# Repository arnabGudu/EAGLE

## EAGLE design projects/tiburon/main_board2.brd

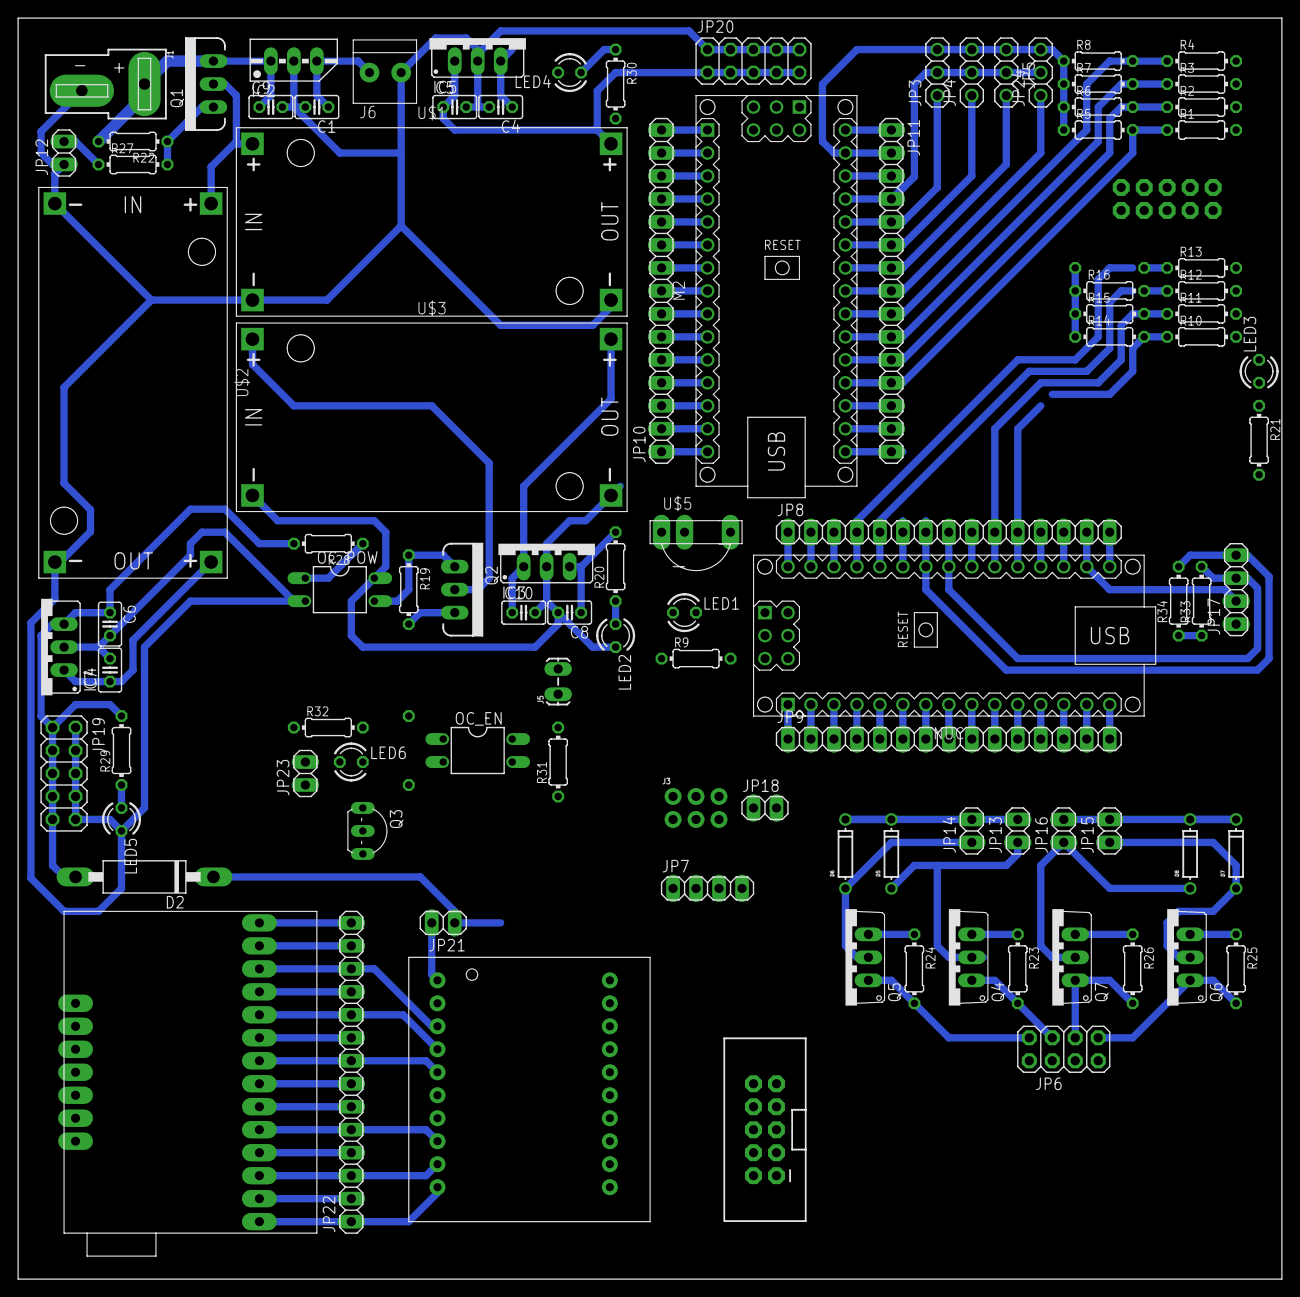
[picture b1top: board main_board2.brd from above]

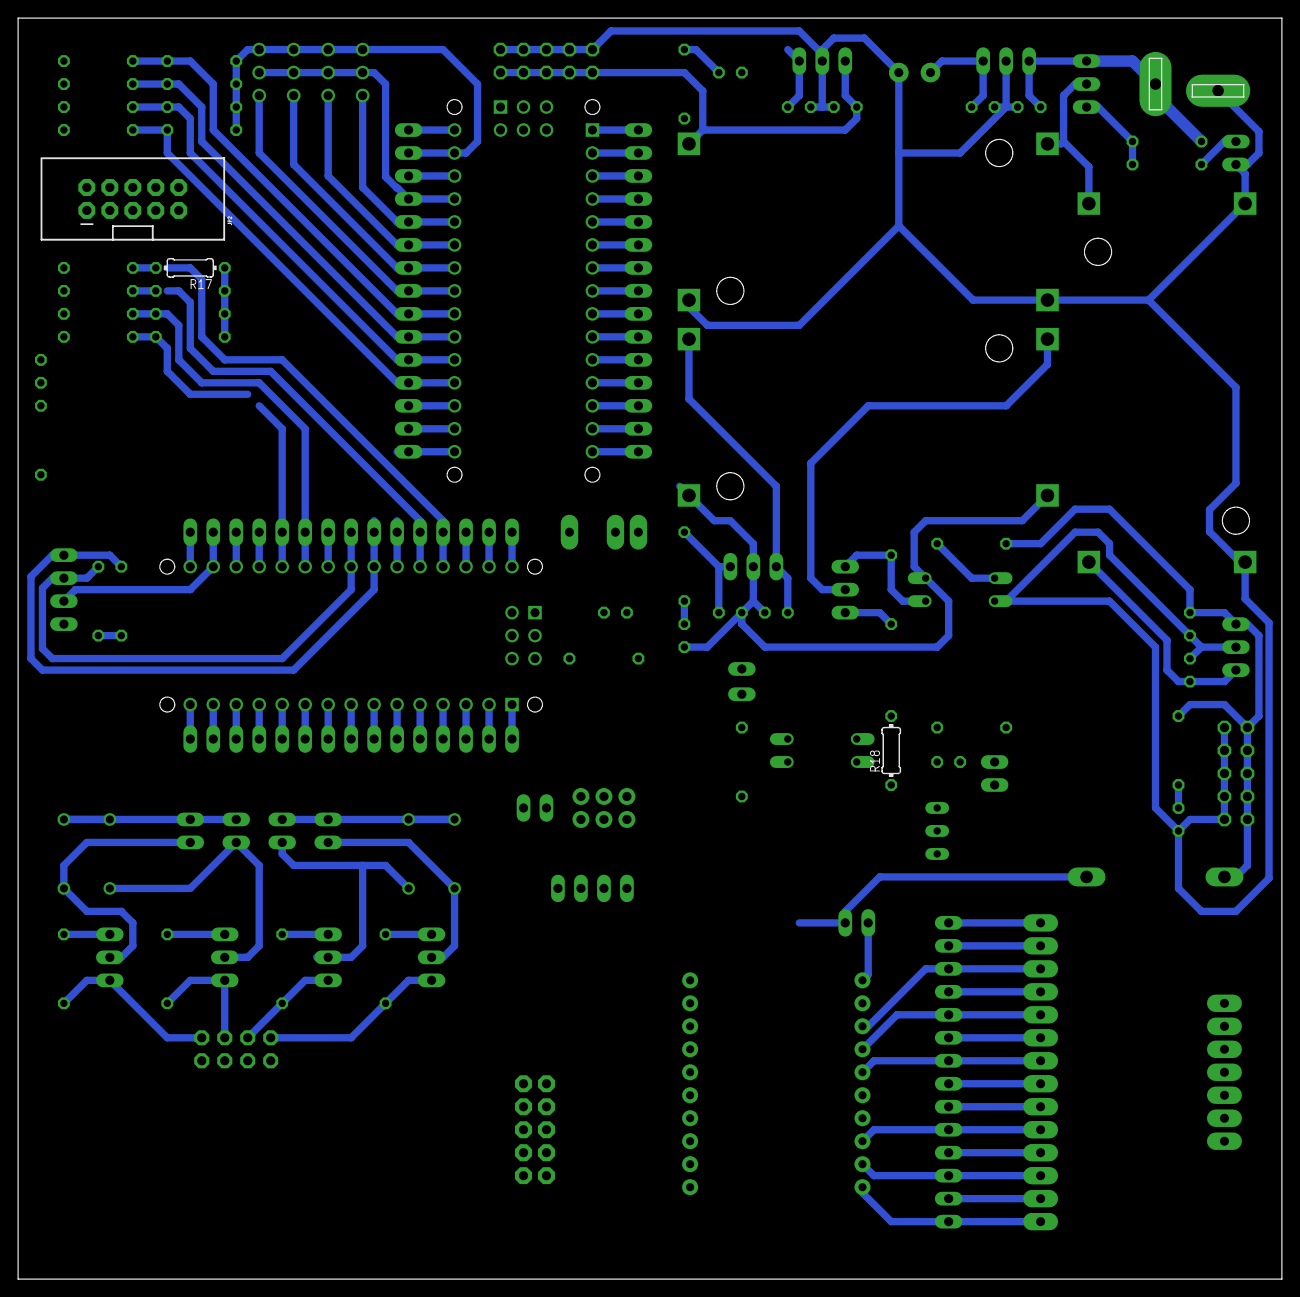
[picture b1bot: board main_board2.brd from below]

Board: 2 copper layers, 139.7 x 139.4 mm, 102 parts (3 on the bottom side), 119 nets.

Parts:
C1, C4, C5, C6, C7, C8, C9, C10: C025-025X050
D2: SCOTTKY; CB417-15
D5, D6, D7, D8: DO-1N4148
IC2: 7812; 78MXXS
IC3, IC4, IC5: 78XXS
J1: DEANS
J3: 2X3-NS
J5: 1X02_LOCK_LONGPADS
J6: 1X2-3.5MM
JP1, JP2: M05X2SHD; 2X5-SHROUDED
JP3, JP4, JP24: 1X03
JP5: Temp Sensor; 1X03
JP6: 2X04
JP7, JP17: 1X04
JP8, JP9, JP10, JP11: 1X15
JP12, JP13, JP14, JP15, JP16, JP21, JP23: 1X02
JP18: Extra Reed; 1X02
JP19, JP20: 2X05
JP22: 1X14
LED1, LED2, LED3, LED4, LED5, LED6: LED3MM
M2: ARDUINO-NANO-3.0#ISP
NUC: ARDUINO-NANO-3.0#ISP
OC_EN: SFH610; DIL04
OC_POW: SFH610; DIL04
Q1, Q2: MOSFET-PCHANNELFQP27P06; TO220V
Q3: BC548; TO92-EBC
Q4, Q5, Q6, Q7: TO220V
R1, R2, R3, R4, R5, R6, R7, R8, R9, R10, R11, R12, R13, R14, R15, R16, R17, R18, R19, R20, R21, R22, R23, R24, R25, R26, R27, R28, R29, R30, R31, R32, R33, R34: 0204/7
U$1, U$2, U$3: DC-DC-STEP-DOWN-LM2596
U$5: TSOP34X; TSOP3XXX
U$6: SERVO_CONTROLLER
U$7: DIGITAL_ISOLATOR; DIGITAL_ISOLATOR_MODULE

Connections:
DR1: JP6.1, Q6.1, R25.2
DR2: JP6.3, Q7.1, R26.2
E16.8V: Q2.3, R19.2
EA0: JP11.12, M2.J2.12, R1.1, R5.2
EA1: JP11.11, M2.J2.11, R2.1, R6.2
EA2: JP11.10, M2.J2.10, R3.1, R7.2
EA3: JP11.9, M2.J2.9, R4.1, R8.2
ED3: JP10.10, M2.J1.6, R9.2
EN: J5.2, OC_EN.4, R31.2
GNDE: C8.2, C10.2, IC3.GND, JP2.2, JP3.3, JP4.3, JP5.3, JP11.2, JP24.3, LED1.K, LED2.K, LED4.K, M2.J2.2, OC_POW.4, Q3.E, R5.1, R6.1, R7.1, R8.1, U$3.IN-, U$3.OUT-, U$7.19
GNDN: C1.2, C4.2, C5.2, C6.2, C7.2, C9.2, IC2.GND, IC4.GND, IC5.GND, J1.-, J6.2, JP2.1, JP8.2, JP12.1, JP17.1, JP18.1, JP19.2, JP19.4, JP19.6, JP19.8, JP19.10, JP20.2, JP20.4, JP20.6, JP20.8, JP20.10, LED3.K, LED5.K, NUC.J2.2, OC_EN.2, OC_POW.2, Q4.3, Q5.3, Q6.3, Q7.3, R14.1, R15.1, R16.1, R17.1, R23.1, R24.1, R25.1, R26.1, U$1.IN-, U$1.OUT-, U$2.IN-, U$2.OUT-, U$5.1, U$6.GND, U$7.2
N6V: C4.1, D7.C, D8.C, IC5.OUT, JP15.2, JP16.2
N12V: C5.1, D5.C, D6.C, IC5.IN, JP13.2, JP14.2, JP20.1, JP20.3, JP20.5, JP20.7, JP20.9, U$1.OUT+
unnamed: JP10.11, M2.J1.5
unnamed: OC_EN.1, R18.1
unnamed: JP9.1, NUC.J1.1
unnamed: JP9.2, NUC.J1.2
unnamed: JP9.3, NUC.J1.3
unnamed: LED1.A, R9.1
unnamed: JP2.10, R1.2
unnamed: JP2.8, R2.2
unnamed: JP2.6, R3.2
unnamed: JP2.4, R4.2
unnamed: JP8.7, JP17.4, NUC.J2.7, R34.2
unnamed: JP8.8, JP17.3, NUC.J2.8, R33.2
unnamed: JP9.4, NUC.J1.4
unnamed: JP9.5, NUC.J1.5
unnamed: JP2.9, R10.2
unnamed: JP2.7, R11.2
unnamed: JP2.5, R12.2
unnamed: JP2.3, R13.2
unnamed: JP9.6, NUC.J1.6
unnamed: OC_POW.3, Q2.1, R19.1
unnamed: JP9.7, NUC.J1.7
unnamed: C10.1, IC3.IN, U$3.OUT+
unnamed: JP22.10, U$6.8, U$7.4
unnamed: Q2.2, U$3.IN+
unnamed: LED2.A, R20.1
unnamed: D2.C, JP8.4, JP21.1, NUC.J2.4
unnamed: Q3.B, R31.1
unnamed: JP9.8, NUC.J1.8
unnamed: JP22.1, U$6.0, U$7.10
unnamed: C9.1, IC2.IN, J1.+, Q1.3, R22.2
unnamed: C1.1, IC2.OUT, J6.1
unnamed: JP22.2, U$6.1
unnamed: JP9.9, NUC.J1.9
unnamed: JP9.10, NUC.J1.10
unnamed: LED4.A, R30.1
unnamed: JP11.1, M2.J2.1
unnamed: JP9.11, NUC.J1.11
unnamed: JP9.12, NUC.J1.12
unnamed: JP9.13, NUC.J1.13
unnamed: JP9.14, NUC.J1.14
unnamed: JP9.15, NUC.J1.15
unnamed: JP22.3, U$6.2, U$7.9
unnamed: J3.6, JP7.3
unnamed: J3.2, JP7.1
unnamed: J3.1, JP7.2
unnamed: J3.5, JP7.4
unnamed: JP8.1, NUC.J2.1
unnamed: JP8.3, NUC.J2.3
unnamed: JP21.2, U$7.1
unnamed: JP8.5, NUC.J2.5
unnamed: JP8.6, NUC.J2.6
unnamed: JP22.4, U$6.3
unnamed: JP22.5, U$6.4, U$7.8
unnamed: JP8.13, NUC.J2.13
unnamed: JP8.14, JP17.2, NUC.J2.14
unnamed: JP8.15, NUC.J2.15, R21.2
unnamed: LED3.A, R21.1
unnamed: JP22.6, U$6.5
unnamed: JP22.7, U$6.+5V(OUT)
unnamed: JP22.8, U$6.6, U$7.5
unnamed: JP22.9, U$6.7
unnamed: Q1.1, R22.1, R27.2
unnamed: JP22.11, U$6.9
unnamed: JP22.12, U$6.10, U$7.3
unnamed: JP22.13, U$6.11
unnamed: JP10.1, M2.J1.15
unnamed: JP10.2, M2.J1.14
unnamed: JP10.3, M2.J1.13
unnamed: JP10.4, M2.J1.12
unnamed: JP10.5, M2.J1.11
unnamed: JP10.6, M2.J1.10
unnamed: JP10.7, M2.J1.9
unnamed: JP10.8, M2.J1.8
unnamed: JP10.9, M2.J1.7
unnamed: JP22.14, U$6.VSRV
unnamed: JP10.12, M2.J1.4
unnamed: JP10.13, M2.J1.3
unnamed: JP10.14, M2.J1.2
unnamed: JP10.15, M2.J1.1
unnamed: JP11.15, M2.J2.15, R30.2
unnamed: JP11.14, M2.J2.14
unnamed: JP11.13, M2.J2.13
unnamed: JP11.3, M2.J2.3
unnamed: D5.A, JP13.1, Q4.2
unnamed: D6.A, JP14.1, Q5.2
unnamed: JP12.2, R27.1
unnamed: D7.A, JP15.1, Q6.2
unnamed: D8.A, JP16.1, Q7.2
unnamed: C7.1, IC4.IN, U$2.OUT+
unnamed: OC_POW.1, R28.1
unnamed: Q1.2, U$1.IN+, U$2.IN+
unnamed: LED5.A, R29.1
unnamed: LED6.K, Q3.C
unnamed: LED6.A, R32.2
NA0: JP8.12, NUC.J2.12, R13.1, R17.2
NA1: JP8.11, NUC.J2.11, R12.1, R16.2
NA2: JP8.10, NUC.J2.10, R11.1, R15.2
NA3: JP8.9, NUC.J2.9, R10.1, R14.2
TMP1: JP11.8, JP24.1, M2.J2.8
TMP2: JP5.1, JP11.7, M2.J2.7
TMP3: JP4.1, JP11.6, M2.J2.6
TMP4: JP3.1, JP11.5, M2.J2.5
TP1: JP6.5, Q4.1, R23.2
TP2: JP6.7, Q5.1, R24.2
VCCE: C8.1, IC3.OUT, J5.1, JP3.2, JP4.2, JP5.2, JP11.4, JP23.1, JP23.2, JP24.2, M2.J2.4, OC_EN.3, R20.2, R32.1, U$7.20
VCCN: C6.1, D2.A, IC4.OUT, JP19.1, JP19.3, JP19.5, JP19.7, JP19.9, R28.2, R29.2, R33.1, R34.1, U$5.2

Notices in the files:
parts and their libraries:
SparkFun-Connectors: Licensing: Creative Commons ShareAlike 4.0 International - https://creativecommons.org/licenses/by-sa/4.0
diy-modules: Released under the Creative Commons Attribution 4.0 International License: http://creativecommons.org/licenses/by/4.0
